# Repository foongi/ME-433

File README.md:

# ME-433
Grad Level Mechatronics at Northwestern

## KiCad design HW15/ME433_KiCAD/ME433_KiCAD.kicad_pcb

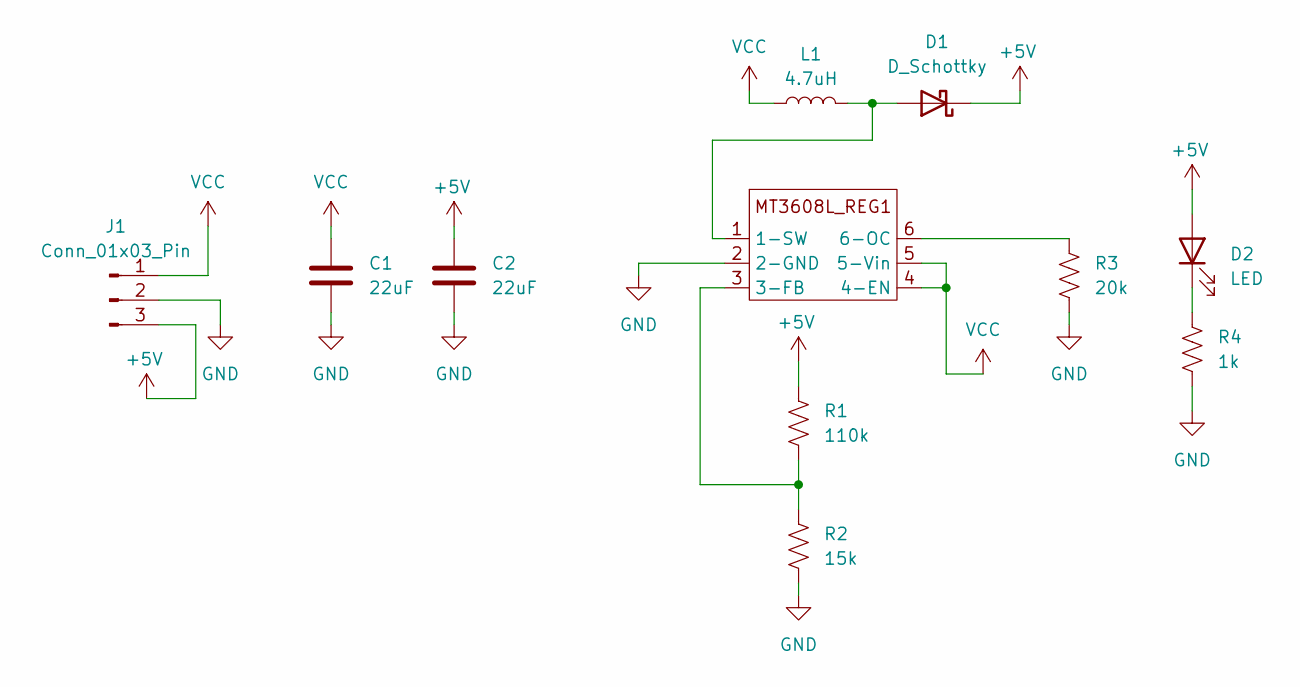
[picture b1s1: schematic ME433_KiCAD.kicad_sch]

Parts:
C1, C2: 22uF; C_1206_3216Metric
D1: D_Schottky; D_SOD-123
D2: LED; LED_D3.0mm
J1: Conn_01x03_Pin; PinSocket_1x03_P2.54mm_Vertical
L1: 4.7uH; L_1206_3216Metric
MT3608L_REG2: SOT-23-6
R1: 110k; R_0402_1005Metric
R2: 15k; R_0402_1005Metric
R3: 20k; R_0402_1005Metric
R4: 1k; R_0402_1005Metric

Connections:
+5V: C2.1, D1.1 (K), D2.2 (A), J1.3, R1.1
GND: C1.2, C2.2, J1.2, MT3608L_REG2.2 (2-GND), R2.2, R3.2, R4.2
unnamed: D1.2 (A), L1.2, MT3608L_REG2.1 (1-SW)
unnamed: D2.1 (K), R4.1
unnamed: MT3608L_REG2.3 (3-FB), R1.2, R2.1
unnamed: MT3608L_REG2.6 (6-OC), R3.1
VCC: C1.1, J1.1, L1.1, MT3608L_REG2.4 (4-EN), MT3608L_REG2.5 (5-Vin)

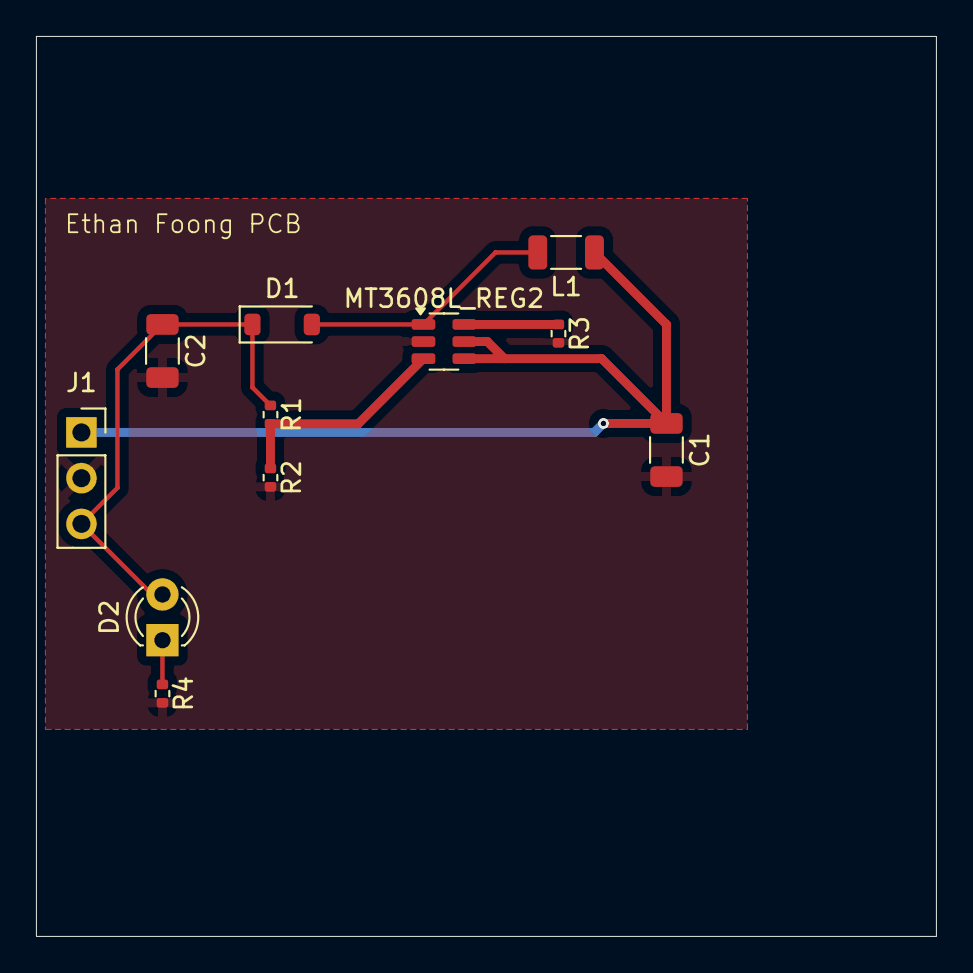
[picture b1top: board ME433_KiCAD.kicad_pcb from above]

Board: 2 copper layers, 50.0 x 50.0 mm, 11 parts (0 on the bottom side), 7 nets.

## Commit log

2025-04-06 Homework 2 of ME 433
2025-04-06 Added ME433 Kitchen to git ignore
2025-04-08 HW 3 Finished
2025-04-11 HW 4 Verified Writing Works
2025-04-11 Finished HW 4 DAC
2025-04-16 HW 4 Clock Cycle Counting
2025-04-16 External RAM Finished
2025-04-16 Changed some timing elements
2025-04-19 Finished External IO HW 6
2025-04-23 Finished draw mesage
2025-04-23 Finished ADC Read and FPS check for HW 7
2025-04-28 Finished HW 8
2025-04-30 Finished Rudamentary multicore
2025-05-03 Finished Filter HW 10
2025-05-03 Changed Gitignore
2025-05-03 Removed env
2025-05-09 Finished Mouse
2025-05-14 Finished Camera and Accelerometer
2025-05-20 Car CAD V1 (Very Rough)
2025-05-27 KiCAD
2025-06-04 Updated Camera and CAD
2025-06-04 Finished Motor control
2025-06-05 Final Project WIP
2025-06-05 Tuning PID Controller
